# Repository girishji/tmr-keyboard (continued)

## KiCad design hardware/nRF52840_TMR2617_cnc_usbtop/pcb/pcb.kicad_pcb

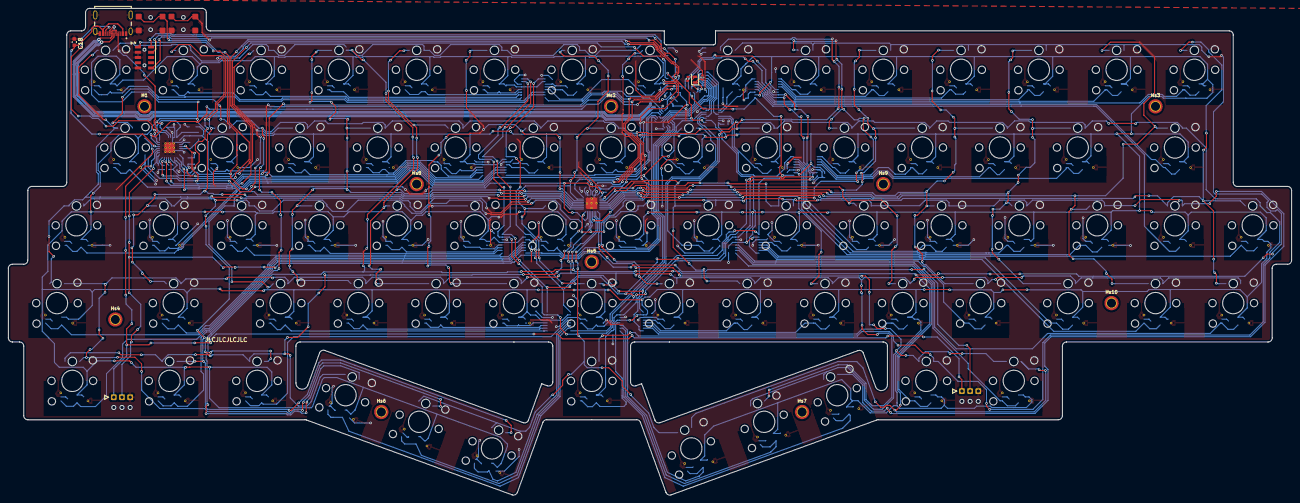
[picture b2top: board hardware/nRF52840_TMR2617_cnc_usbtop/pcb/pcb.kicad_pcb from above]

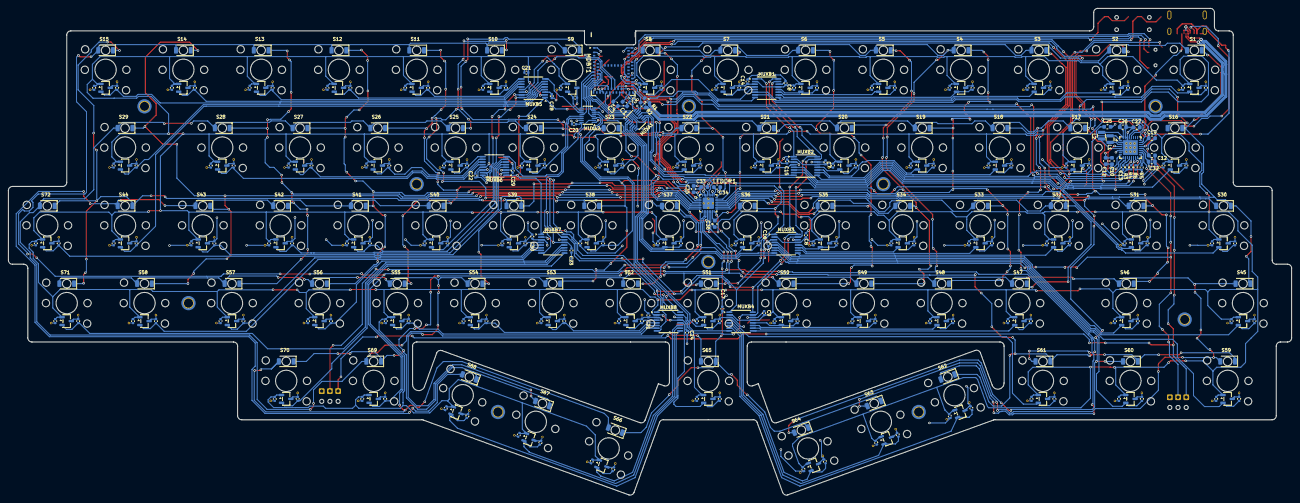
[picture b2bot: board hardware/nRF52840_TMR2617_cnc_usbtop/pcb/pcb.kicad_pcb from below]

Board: 2 copper layers, 313.5 x 118.9 mm, 437 parts (342 on the bottom side), 146 nets.

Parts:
BAT1, BAT2: PCB_Wire_Solder_3p_Connector
C1, C3, C10, C11, C12, C25, C26: 10uF; C_0603_1608Metric
C2, C4: 12pF; C_0402_1005Metric
C5, C6, C7, C8, C9, C14, C15, C16, C17, C20, C21, C22, C23, C24, C28, C29, C30, C31: .1uF; C_0402_1005Metric
C13: 0.1uF; C_0402_1005Metric
C18, C19, C34, C35, C36: 1uF; C_0603_1608Metric
C27, C32: 2.2uF; C_0603_1608Metric
C33: 1nF; C_0603_1608Metric
Cvcc1, Cvcc2, Cvcc3, Cvcc4, Cvcc5, Cvcc6, Cvcc7, Cvcc8, Cvcc9, Cvcc10, Cvcc11, Cvcc12, Cvcc13, Cvcc14, Cvcc15, Cvcc16, Cvcc17, Cvcc18, Cvcc19, Cvcc20, Cvcc21, Cvcc22, Cvcc23, Cvcc24, Cvcc25, Cvcc26, Cvcc27, Cvcc28, Cvcc29, Cvcc30, Cvcc31, Cvcc32, Cvcc33, Cvcc34, Cvcc35, Cvcc36, Cvcc37, Cvcc38, Cvcc39, Cvcc40, Cvcc41, Cvcc42, Cvcc43, Cvcc44, Cvcc45, Cvcc46, Cvcc47, Cvcc48, Cvcc49, Cvcc50, Cvcc51, Cvcc52, Cvcc53, Cvcc54, Cvcc55, Cvcc56, Cvcc57, Cvcc58, Cvcc59, Cvcc60, Cvcc61, Cvcc62, Cvcc63, Cvcc64, Cvcc65, Cvcc66, Cvcc67, Cvcc68, Cvcc69, Cvcc70, Cvcc71, Cvcc72: 0.1uF; C_0402_1005Metric_Cvcc
Cvout1, Cvout2, Cvout3, Cvout4, Cvout5, Cvout6, Cvout7, Cvout8, Cvout9, Cvout10, Cvout11, Cvout12, Cvout13, Cvout14, Cvout15, Cvout16, Cvout17, Cvout18, Cvout19, Cvout20, Cvout21, Cvout22, Cvout23, Cvout24, Cvout25, Cvout26, Cvout27, Cvout28, Cvout29, Cvout30, Cvout31, Cvout32, Cvout33, Cvout34, Cvout35, Cvout36, Cvout37, Cvout38, Cvout39, Cvout40, Cvout41, Cvout42, Cvout43, Cvout44, Cvout45, Cvout46, Cvout47, Cvout48, Cvout49, Cvout50, Cvout51, Cvout52, Cvout53, Cvout54, Cvout55, Cvout56, Cvout57, Cvout58, Cvout59, Cvout60, Cvout61, Cvout62, Cvout63, Cvout64, Cvout65, Cvout66, Cvout67, Cvout68, Cvout69, Cvout70, Cvout71, Cvout72: 0.1nF; C_0402_1005Metric_Cvout
D1, D2, D3, D4, D5, D6, D7, D8, D9, D10, D11, D12, D13, D14, D15, D16, D17, D18, D19, D20, D21, D22, D23, D24, D25, D26, D27, D28, D29, D30, D31, D32, D33, D34, D35, D36, D37, D38, D39, D40, D41, D42, D43, D44, D45, D46, D47, D48, D49, D50, D51, D52, D53, D54, D55, D56, D57, D58, D59, D60, D61, D62, D63, D64, D65, D66, D67, D68, D69, D70, D71, D72: Green LED; LED_1206_3216Metric_ReverseMount_Hole2.1mm
H1: M2_Pad; MountingHole_2.2mm_M2_ISO7380_Pad_TopBottom
Hs2, Hs3, Hs4, Hs5, Hs6, Hs7, Hs8, Hs9, Hs10: M2_Pad; MountingHole_2.2mm_M2_ISO7380_Pad_TopBottom
JLC1: JLC_Order_Num
JTAG1: Conn_ARM_JTAG_SWD_10; SAMTEC-CLP-105-02-X-D-A
Jusb1: USB_TYPE_C_Receptacle_16P; GCT_USB4215-03-A_REVA
L1, L2: 2.2uH; L_Samsung_CIGT201610EH2R2MNE
LEDDR1: LP5864; LP5864-VQFN-32-1EP_4x4mm_P0.4mm_EP2.8x2.8mm_ThermalVias
MDBT1: Raytac_MDBT50Q
MUXA1, MUXA2: TMUX1574DYY; Texas_DYY0016A_TSOT-23-16_2x4.2mm_P0.5mm
MUXB1, MUXB2, MUXB3, MUXB4, MUXB5, MUXB6, MUXB7, MUXB8: TMUX1108PW; TSSOP-16_4.4x5mm_P0.65mm
PMIC1: nPM1300-QEXX; QFN-32-1EP_5x5mm_P0.5mm_EP3.6x3.6mm_ThermalVias
R1, R2: 27R; R_0603_1608Metric
R3, R4: 10k; R_0402_1005Metric
R5, R6: 47k; R_0402_1005Metric
S1, S2, S3, S4, S5, S6, S7, S8, S9, S10, S11, S12, S13, S14, S15, S16, S17, S18, S19, S20, S21, S22, S23, S24, S25, S26, S27, S28, S29, S30, S31, S32, S33, S34, S35, S36, S37, S38, S39, S40, S41, S42, S43, S44, S45, S46, S47, S48, S49, S50, S51, S52, S53, S54, S55, S56, S57, S58, S59, S60, S61, S62, S63, S64, S65, S66, S67, S68, S69, S70, S71, S72: Switch; Gateron_Kailh_Lowpro_Switch
SW1, SW2: SW_DIP_x01; Aliexpress_SW_DIP_TS_1292V_4x6.2x1.8mm
Stb1, Stb2: TMR_switch_stab_2.0u; Stabilizer_Lowpro_2U
TMR1, TMR2, TMR3, TMR4, TMR5, TMR6, TMR7, TMR8, TMR9, TMR10, TMR11, TMR12, TMR13, TMR14, TMR15, TMR16, TMR17, TMR18, TMR19, TMR20, TMR21, TMR22, TMR23, TMR24, TMR25, TMR26, TMR27, TMR28, TMR29, TMR30, TMR31, TMR32, TMR33, TMR34, TMR35, TMR36, TMR37, TMR38, TMR39, TMR40, TMR41, TMR42, TMR43, TMR44, TMR45, TMR46, TMR47, TMR48, TMR49, TMR50, TMR51, TMR52, TMR53, TMR54, TMR55, TMR56, TMR57, TMR58, TMR59, TMR60, TMR61, TMR62, TMR63, TMR64, TMR65, TMR66, TMR67, TMR68, TMR69, TMR70, TMR71, TMR72: TMR2617; SOT-23-3
Y1: 32.768 kHz; Crystal_SMD_2012-2Pin_2.0x1.2mm

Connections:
/AIN0: MDBT1.11 (P0.02/AIN0), MUXA1.4 (D1)
/AIN1: MDBT1.9 (P0.03/AIN1), MUXA1.7 (D2)
/AIN2: MDBT1.20 (P0.04/AIN2), MUXA1.12 (D4)
/AIN3: MDBT1.21 (P0.05/AIN3), MUXA1.9 (D3)
/AIN4: MDBT1.13 (P0.28/AIN4), MUXA2.7 (D2)
/AIN5: MDBT1.10 (P0.29/AIN5), MUXA2.9 (D3)
/AIN6: MDBT1.14 (P0.30/AIN6), MUXA2.4 (D1)
/AIN7: MDBT1.12 (P0.31/AIN7), MUXA2.12 (D4)
/ANA_01: Cvout1.1, MUXB1.7 (S4), TMR1.2 (V_{OUT})
/ANA_02: Cvout2.1, MUXB1.6 (S3), TMR2.2 (V_{OUT})
/ANA_03: Cvout3.1, MUXB1.9 (S8), TMR3.2 (V_{OUT})
/ANA_04: Cvout4.1, MUXB1.10 (S7), TMR4.2 (V_{OUT})
/ANA_05: Cvout5.1, MUXB1.11 (S6), TMR5.2 (V_{OUT})
/ANA_06: Cvout6.1, MUXB1.12 (S5), TMR6.2 (V_{OUT})
/ANA_07: Cvout7.1, MUXB1.4 (S1), TMR7.2 (V_{OUT})
/ANA_08: Cvout8.1, MUXB1.5 (S2), TMR8.2 (V_{OUT})
/ANA_09: Cvout9.1, MUXA2.10 (S3B), TMR9.2 (V_{OUT})
/ANA_10: Cvout10.1, MUXB5.9 (S8), TMR10.2 (V_{OUT})
/ANA_11: Cvout11.1, MUXB5.10 (S7), TMR11.2 (V_{OUT})
/ANA_12: Cvout12.1, MUXB5.11 (S6), TMR12.2 (V_{OUT})
/ANA_13: Cvout13.1, MUXB5.12 (S5), TMR13.2 (V_{OUT})
/ANA_14: Cvout14.1, MUXB5.7 (S4), TMR14.2 (V_{OUT})
/ANA_15: Cvout15.1, MUXB5.6 (S3), TMR15.2 (V_{OUT})
/ANA_16: Cvout16.1, MUXB2.5 (S2), TMR16.2 (V_{OUT})
/ANA_17: Cvout17.1, MUXB2.9 (S8), TMR17.2 (V_{OUT})
/ANA_18: Cvout18.1, MUXB2.10 (S7), TMR18.2 (V_{OUT})
/ANA_19: Cvout19.1, MUXB2.11 (S6), TMR19.2 (V_{OUT})
/ANA_20: Cvout20.1, MUXB2.12 (S5), TMR20.2 (V_{OUT})
/ANA_21: Cvout21.1, MUXB2.4 (S1), TMR21.2 (V_{OUT})
/ANA_22: Cvout22.1, MUXA1.13 (S4B), TMR22.2 (V_{OUT})
/ANA_23: Cvout23.1, MUXA2.6 (S2B), TMR23.2 (V_{OUT})
/ANA_24: Cvout24.1, MUXA2.13 (S4B), TMR24.2 (V_{OUT})
/ANA_25: Cvout25.1, MUXB6.9 (S8), TMR25.2 (V_{OUT})
/ANA_26: Cvout26.1, MUXB6.10 (S7), TMR26.2 (V_{OUT})
/ANA_27: Cvout27.1, MUXB6.11 (S6), TMR27.2 (V_{OUT})
/ANA_28: Cvout28.1, MUXB6.12 (S5), TMR28.2 (V_{OUT})
/ANA_29: Cvout29.1, MUXB5.5 (S2), TMR29.2 (V_{OUT})
/ANA_30: Cvout30.1, MUXB2.7 (S4), TMR30.2 (V_{OUT})
/ANA_31: Cvout31.1, MUXB2.6 (S3), TMR31.2 (V_{OUT})
/ANA_32: Cvout32.1, MUXB3.9 (S8), TMR32.2 (V_{OUT})
/ANA_33: Cvout33.1, MUXB3.10 (S7), TMR33.2 (V_{OUT})
/ANA_34: Cvout34.1, MUXB3.11 (S6), TMR34.2 (V_{OUT})
/ANA_35: Cvout35.1, MUXB3.12 (S5), TMR35.2 (V_{OUT})
/ANA_36: Cvout36.1, MUXA1.6 (S2B), TMR36.2 (V_{OUT})
/ANA_37: Cvout37.1, MUXA1.10 (S3B), TMR37.2 (V_{OUT})
/ANA_38: Cvout38.1, MUXA2.3 (S1B), TMR38.2 (V_{OUT})
/ANA_39: Cvout39.1, MUXB7.4 (S1), TMR39.2 (V_{OUT})
/ANA_40: Cvout40.1, MUXB6.7 (S4), TMR40.2 (V_{OUT})
/ANA_41: Cvout41.1, MUXB6.6 (S3), TMR41.2 (V_{OUT})
/ANA_42: Cvout42.1, MUXB6.5 (S2), TMR42.2 (V_{OUT})
/ANA_43: Cvout43.1, MUXB6.4 (S1), TMR43.2 (V_{OUT})
/ANA_44: Cvout44.1, MUXB5.4 (S1), TMR44.2 (V_{OUT})
/ANA_45: Cvout45.1, MUXB3.5 (S2), TMR45.2 (V_{OUT})
/ANA_46: Cvout46.1, MUXB3.4 (S1), TMR46.2 (V_{OUT})
/ANA_47: Cvout47.1, MUXB4.9 (S8), TMR47.2 (V_{OUT})
/ANA_48: Cvout48.1, MUXB4.10 (S7), TMR48.2 (V_{OUT})
/ANA_49: Cvout49.1, MUXB4.11 (S6), TMR49.2 (V_{OUT})
/ANA_50: Cvout50.1, MUXB4.12 (S5), TMR50.2 (V_{OUT})
/ANA_51: Cvout51.1, MUXA1.3 (S1B), TMR51.2 (V_{OUT})
/ANA_52: Cvout52.1, MUXB8.4 (S1), TMR52.2 (V_{OUT})
/ANA_53: Cvout53.1, MUXB8.5 (S2), TMR53.2 (V_{OUT})
/ANA_54: Cvout54.1, MUXB8.6 (S3), TMR54.2 (V_{OUT})
/ANA_55: Cvout55.1, MUXB8.7 (S4), TMR55.2 (V_{OUT})
/ANA_56: Cvout56.1, MUXB7.12 (S5), TMR56.2 (V_{OUT})
/ANA_57: Cvout57.1, MUXB7.6 (S3), TMR57.2 (V_{OUT})
/ANA_58: Cvout58.1, MUXB7.7 (S4), TMR58.2 (V_{OUT})
/ANA_59: Cvout59.1, MUXB3.6 (S3), TMR59.2 (V_{OUT})
/ANA_60: Cvout60.1, MUXB3.7 (S4), TMR60.2 (V_{OUT})
/ANA_61: Cvout61.1, MUXB4.4 (S1), TMR61.2 (V_{OUT})
/ANA_62: Cvout62.1, MUXB4.7 (S4), TMR62.2 (V_{OUT})
/ANA_63: Cvout63.1, MUXB4.6 (S3), TMR63.2 (V_{OUT})
/ANA_64: Cvout64.1, MUXB4.5 (S2), TMR64.2 (V_{OUT})
/ANA_65: Cvout65.1, MUXB8.12 (S5), TMR65.2 (V_{OUT})
/ANA_66: Cvout66.1, MUXB8.11 (S6), TMR66.2 (V_{OUT})
/ANA_67: Cvout67.1, MUXB8.10 (S7), TMR67.2 (V_{OUT})
/ANA_68: Cvout68.1, MUXB8.9 (S8), TMR68.2 (V_{OUT})
/ANA_69: Cvout69.1, MUXB7.9 (S8), TMR69.2 (V_{OUT})
/ANA_70: Cvout70.1, MUXB7.10 (S7), TMR70.2 (V_{OUT})
/ANA_71: Cvout71.1, MUXB7.11 (S6), TMR71.2 (V_{OUT})
/ANA_72: Cvout72.1, MUXB7.5 (S2), TMR72.2 (V_{OUT})
/CS0: D9.1 (K), D24.1 (K), D38.1 (K), D53.1 (K), LEDDR1.2 (CS0)
/CS1: D10.1 (K), D25.1 (K), D39.1 (K), D54.1 (K), LEDDR1.3 (CS1)
/CS2: D11.1 (K), D26.1 (K), D40.1 (K), D55.1 (K), LEDDR1.4 (CS2)
/CS3: D12.1 (K), D27.1 (K), D41.1 (K), D56.1 (K), LEDDR1.5 (CS3)
/CS4: D13.1 (K), D28.1 (K), D42.1 (K), D57.1 (K), LEDDR1.6 (CS4)
/CS5: D14.1 (K), D29.1 (K), D43.1 (K), D58.1 (K), LEDDR1.7 (CS5)
/CS6: D15.1 (K), D44.1 (K), D71.1 (K), D72.1 (K), LEDDR1.8 (CS6)
/CS7: D67.1 (K), D68.1 (K), D69.1 (K), D70.1 (K), LEDDR1.9 (CS7)
/CS8: D63.1 (K), D64.1 (K), D65.1 (K), D66.1 (K), LEDDR1.10 (CS8)
/CS9: D59.1 (K), D60.1 (K), D61.1 (K), D62.1 (K), LEDDR1.16 (CS9)
/CS10: D1.1 (K), D16.1 (K), D30.1 (K), D45.1 (K), LEDDR1.17 (CS10)
/CS11: D2.1 (K), D17.1 (K), D31.1 (K), D46.1 (K), LEDDR1.18 (CS11)
/CS12: D3.1 (K), D18.1 (K), D32.1 (K), D47.1 (K), LEDDR1.19 (CS12)
/CS13: D4.1 (K), D19.1 (K), D33.1 (K), D48.1 (K), LEDDR1.20 (CS13)
/CS14: D5.1 (K), D20.1 (K), D34.1 (K), D49.1 (K), LEDDR1.21 (CS14)
/CS15: D6.1 (K), D21.1 (K), D35.1 (K), D50.1 (K), LEDDR1.22 (CS15)
/CS16: D7.1 (K), D22.1 (K), D36.1 (K), D51.1 (K), LEDDR1.23 (CS16)
/CS17: D8.1 (K), D23.1 (K), D37.1 (K), D52.1 (K), LEDDR1.24 (CS17)
/GPIO_X: MDBT1.38 (P0.16), PMIC1.10 (GPIO3)
/INT: MDBT1.36 (P0.14), PMIC1.8 (GPIO1)
/LED_DR_EN: C33.1, LEDDR1.32 (VIO_EN), MDBT1.37 (P0.13)
/LOADSW_CTRL: MDBT1.39 (P0.15), PMIC1.9 (GPIO2)
/MUXA_SEL: MDBT1.41 (P0.17), MUXA1.1 (SEL), MUXA2.1 (SEL)
/MUXB_SEL_0: MDBT1.22 (P0.06), MUXB1.1 (A0), MUXB2.1 (A0), MUXB3.1 (A0), MUXB4.1 (A0), MUXB5.1 (A0), MUXB6.1 (A0), MUXB7.1 (A0), MUXB8.1 (A0)
/MUXB_SEL_1: MDBT1.23 (P0.07), MUXB1.16 (A1), MUXB2.16 (A1), MUXB3.16 (A1), MUXB4.16 (A1), MUXB5.16 (A1), MUXB6.16 (A1), MUXB7.16 (A1), MUXB8.16 (A1)
/MUXB_SEL_2: MDBT1.25 (P1.08), MUXB1.15 (A2), MUXB2.15 (A2), MUXB3.15 (A2), MUXB4.15 (A2), MUXB5.15 (A2), MUXB6.15 (A2), MUXB7.15 (A2), MUXB8.15 (A2)
/MUX_B_1: MUXA1.14 (S4A), MUXB1.8 (D)
/MUX_B_2: MUXA1.11 (S3A), MUXB2.8 (D)
/MUX_B_3: MUXA1.5 (S2A), MUXB3.8 (D)
/MUX_B_4: MUXA1.2 (S1A), MUXB4.8 (D)
/MUX_B_5: MUXA2.11 (S3A), MUXB5.8 (D)
/MUX_B_6: MUXA2.14 (S4A), MUXB6.8 (D)
/MUX_B_7: MUXA2.2 (S1A), MUXB7.8 (D)
/MUX_B_8: MUXA2.5 (S2A), MUXB8.8 (D)
/NRESET: JTAG1.10 (~RESET), MDBT1.40 (P0.18/RESET), SW1.2
/SCL: LEDDR1.28 (SCL_SCLK), MDBT1.27 (P0.11), PMIC1.14 (SCL), R3.2
/SDA: LEDDR1.29 (SDA_MOSI), MDBT1.29 (P0.12), PMIC1.13 (SDA), R4.2
/SW0: D1.2 (A), D2.2 (A), D3.2 (A), D4.2 (A), D5.2 (A), D6.2 (A), D7.2 (A), D8.2 (A), D9.2 (A), D10.2 (A), D11.2 (A), D12.2 (A), D13.2 (A), D14.2 (A), D15.2 (A), D62.2 (A), D66.2 (A), D70.2 (A), LEDDR1.11 (SW0)
/SW1: D16.2 (A), D17.2 (A), D18.2 (A), D19.2 (A), D20.2 (A), D21.2 (A), D22.2 (A), D23.2 (A), D24.2 (A), D25.2 (A), D26.2 (A), D27.2 (A), D28.2 (A), D29.2 (A), D61.2 (A), D65.2 (A), D69.2 (A), D72.2 (A), LEDDR1.12 (SW1)
/SW2: D30.2 (A), D31.2 (A), D32.2 (A), D33.2 (A), D34.2 (A), D35.2 (A), D36.2 (A), D37.2 (A), D38.2 (A), D39.2 (A), D40.2 (A), D41.2 (A), D42.2 (A), D43.2 (A), D44.2 (A), D60.2 (A), D64.2 (A), D68.2 (A), LEDDR1.13 (SW2)
/SW3: D45.2 (A), D46.2 (A), D47.2 (A), D48.2 (A), D49.2 (A), D50.2 (A), D51.2 (A), D52.2 (A), D53.2 (A), D54.2 (A), D55.2 (A), D56.2 (A), D57.2 (A), D58.2 (A), D59.2 (A), D63.2 (A), D67.2 (A), D71.2 (A), LEDDR1.14 (SW3)
/SWDCLK: JTAG1.4 (SWCLK/TCK), MDBT1.53 (SWDCLK)
/SWDIO: JTAG1.2 (SWDIO/TMS), MDBT1.51 (SWDIO)
/USB_D+: Jusb1.A6 (D1+), Jusb1.B6 (D2+), R1.2
/USB_D-: Jusb1.A7 (D1-), Jusb1.B7 (D2-), R2.2
/VBAT: BAT1.1 (VBAT), BAT2.1 (VBAT), C32.1, PMIC1.19 (VBAT)
/VBUSOUT: C1.1, C19.1, MDBT1.32 (VBUS), PMIC1.22 (VBUSOUT)
/VDD_nRF: C3.1, C13.2, C25.1, JTAG1.1 (VTref), L1.1, MDBT1.28 (VDD), MDBT1.30 (VDDH), PMIC1.1 (VOUT1), PMIC1.12 (VDDIO), R3.1, R4.1
/VOUT2: C26.1, L2.1, PMIC1.28 (LSIN1/VINLDO1), PMIC1.32 (VOUT2)
/VSYS: C10.1, C11.1, C12.1, C35.1, C36.1, LEDDR1.1 (VCC), LEDDR1.15 (VLED), PMIC1.4 (PVDD), PMIC1.20 (VSYS)
GND: BAT1.3 (GND), BAT2.3 (GND), C1.2, C2.2, C3.2, C4.2, C5.1, C6.1, C7.1, C8.1, C9.1, C10.2, C11.2, C12.2, C13.1, C14.1, C14.2, C15.1, C15.2, C16.1, C16.2, C17.1, C17.2, C18.2, C19.2, C20.1, C21.1, C22.1, C23.1, C24.1, C25.2, C26.2, C27.2, C28.1, C28.2, C29.1, C29.2, C30.1, C30.2, C31.1, C31.2, C32.2, C33.2, C34.1, C35.2, C36.2, Cvcc1.2, Cvcc2.2, Cvcc3.2, Cvcc4.2, Cvcc5.2, Cvcc6.2, Cvcc7.2, Cvcc8.2, Cvcc9.2, Cvcc10.2, Cvcc11.2, Cvcc12.2, Cvcc13.2, Cvcc14.2, Cvcc15.2, Cvcc16.2, Cvcc17.2, Cvcc18.2, Cvcc19.2, Cvcc20.2, Cvcc21.2, Cvcc22.2, Cvcc23.2, Cvcc24.2, Cvcc25.2, Cvcc26.2, Cvcc27.2, Cvcc28.2, Cvcc29.2, Cvcc30.2, Cvcc31.2, Cvcc32.2, Cvcc33.2, Cvcc34.2, Cvcc35.2, Cvcc36.2, Cvcc37.2, Cvcc38.2, Cvcc39.2, Cvcc40.2, Cvcc41.2, Cvcc42.2, Cvcc43.2, Cvcc44.2, Cvcc45.2, Cvcc46.2, Cvcc47.2, Cvcc48.2, Cvcc49.2, Cvcc50.2, Cvcc51.2, Cvcc52.2, Cvcc53.2, Cvcc54.2, Cvcc55.2, Cvcc56.2, Cvcc57.2, Cvcc58.2, Cvcc59.2, Cvcc60.2, Cvcc61.2, Cvcc62.2, Cvcc63.2, Cvcc64.2, Cvcc65.2, Cvcc66.2, Cvcc67.2, Cvcc68.2, Cvcc69.2, Cvcc70.2, Cvcc71.2, Cvcc72.2, Cvout1.2, Cvout2.2, Cvout3.2, Cvout4.2, Cvout5.2, Cvout6.2, Cvout7.2, Cvout8.2, Cvout9.2, Cvout10.2, Cvout11.2, Cvout12.2, Cvout13.2, Cvout14.2, Cvout15.2, Cvout16.2, Cvout17.2, Cvout18.2, Cvout19.2, Cvout20.2, Cvout21.2, Cvout22.2, Cvout23.2, Cvout24.2, Cvout25.2, Cvout26.2, Cvout27.2, Cvout28.2, Cvout29.2, Cvout30.2, Cvout31.2, Cvout32.2, Cvout33.2, Cvout34.2, Cvout35.2, Cvout36.2, Cvout37.2, Cvout38.2, Cvout39.2, Cvout40.2, Cvout41.2, Cvout42.2, Cvout43.2, Cvout44.2, Cvout45.2, Cvout46.2, Cvout47.2, Cvout48.2, Cvout49.2, Cvout50.2, Cvout51.2, Cvout52.2, Cvout53.2, Cvout54.2, Cvout55.2, Cvout56.2, Cvout57.2, Cvout58.2, Cvout59.2, Cvout60.2, Cvout61.2, Cvout62.2, Cvout63.2, Cvout64.2, Cvout65.2, Cvout66.2, Cvout67.2, Cvout68.2, Cvout69.2, Cvout70.2, Cvout71.2, Cvout72.2, JTAG1.3 (GND), JTAG1.5 (GND), JTAG1.9 (GNDDetect), Jusb1.A1 (GND), Jusb1.A12 (GND), Jusb1.B1 (GND), Jusb1.B12 (GND), Jusb1.S1 (SHIELD), LEDDR1.26 (IFS), LEDDR1.27 (VSYNC), LEDDR1.30 (ADDR0_MISO), LEDDR1.31 (ADDR1_SS), LEDDR1.33 (GND), MDBT1.1 (GND@1), MDBT1.2 (GND@2), MDBT1.15 (GND@15), MDBT1.33 (GND@33), MDBT1.55 (GND@55), MUXA1.8 (GND), MUXA1.15 (~EN), MUXA2.8 (GND), MUXA2.15 (~EN), MUXB1.3 (VSS), MUXB1.14 (GND), MUXB2.3 (VSS), MUXB2.14 (GND), MUXB3.3 (VSS), MUXB3.14 (GND), MUXB4.3 (VSS), MUXB4.14 (GND), MUXB5.3 (VSS), MUXB5.14 (GND), MUXB6.3 (VSS), MUXB6.14 (GND), MUXB7.3 (VSS), MUXB7.14 (GND), MUXB8.3 (VSS), MUXB8.14 (GND), PMIC1.2 (PVSS1), PMIC1.6 (PVSS2), PMIC1.30 (LSIN2/VINLDO2), PMIC1.31 (LSOUT2/VOUTLDO2), PMIC1.33 (AVSS), R5.1, R6.1, SW1.1, SW2.1, TMR1.3 (GND), TMR2.3 (GND), TMR3.3 (GND), TMR4.3 (GND), TMR5.3 (GND), TMR6.3 (GND), TMR7.3 (GND), TMR8.3 (GND), TMR9.3 (GND), TMR10.3 (GND), TMR11.3 (GND), TMR12.3 (GND), TMR13.3 (GND), TMR14.3 (GND), TMR15.3 (GND), TMR16.3 (GND), TMR17.3 (GND), TMR18.3 (GND), TMR19.3 (GND), TMR20.3 (GND), TMR21.3 (GND), TMR22.3 (GND), TMR23.3 (GND), TMR24.3 (GND), TMR25.3 (GND), TMR26.3 (GND), TMR27.3 (GND), TMR28.3 (GND), TMR29.3 (GND), TMR30.3 (GND), TMR31.3 (GND), TMR32.3 (GND), TMR33.3 (GND), TMR34.3 (GND), TMR35.3 (GND), TMR36.3 (GND), TMR37.3 (GND), TMR38.3 (GND), TMR39.3 (GND), TMR40.3 (GND), TMR41.3 (GND), TMR42.3 (GND), TMR43.3 (GND), TMR44.3 (GND), TMR45.3 (GND), TMR46.3 (GND), TMR47.3 (GND), TMR48.3 (GND), TMR49.3 (GND), TMR50.3 (GND), TMR51.3 (GND), TMR52.3 (GND), TMR53.3 (GND), TMR54.3 (GND), TMR55.3 (GND), TMR56.3 (GND), TMR57.3 (GND), TMR58.3 (GND), TMR59.3 (GND), TMR60.3 (GND), TMR61.3 (GND), TMR62.3 (GND), TMR63.3 (GND), TMR64.3 (GND), TMR65.3 (GND), TMR66.3 (GND), TMR67.3 (GND), TMR68.3 (GND), TMR69.3 (GND), TMR70.3 (GND), TMR71.3 (GND), TMR72.3 (GND)
unnamed: BAT1.2 (NTC), BAT2.2 (NTC), PMIC1.18 (NTC)
unnamed: Jusb1.A5 (CC1), PMIC1.23 (CC1)
unnamed: Jusb1.B5 (CC2), PMIC1.24 (CC2)
unnamed: C34.2, LEDDR1.25 (VCAP)
unnamed: MDBT1.35 (D+), R1.1
unnamed: MDBT1.34 (D-), R2.1
unnamed: C2.1, MDBT1.17 (P0.00/XL1), Y1.1
unnamed: C4.1, MDBT1.18 (P0.01/XL2), Y1.2
unnamed: PMIC1.15 (SHPHLD), SW2.2
unnamed: L1.2, PMIC1.3 (SW1)
unnamed: L2.2, PMIC1.5 (SW2)
unnamed: C18.1, Jusb1.A4 (VBUS), Jusb1.A9 (VBUS), Jusb1.B4 (VBUS), Jusb1.B9 (VBUS), PMIC1.21 (VBUS)
unnamed: PMIC1.17 (VSET1), R5.2
unnamed: PMIC1.16 (VSET2), R6.2
VCCS: C5.2, C6.2, C7.2, C8.2, C9.2, C20.2, C21.2, C22.2, C23.2, C24.2, C27.1, Cvcc1.1, Cvcc2.1, Cvcc3.1, Cvcc4.1, Cvcc5.1, Cvcc6.1, Cvcc7.1, Cvcc8.1, Cvcc9.1, Cvcc10.1, Cvcc11.1, Cvcc12.1, Cvcc13.1, Cvcc14.1, Cvcc15.1, Cvcc16.1, Cvcc17.1, Cvcc18.1, Cvcc19.1, Cvcc20.1, Cvcc21.1, Cvcc22.1, Cvcc23.1, Cvcc24.1, Cvcc25.1, Cvcc26.1, Cvcc27.1, Cvcc28.1, Cvcc29.1, Cvcc30.1, Cvcc31.1, Cvcc32.1, Cvcc33.1, Cvcc34.1, Cvcc35.1, Cvcc36.1, Cvcc37.1, Cvcc38.1, Cvcc39.1, Cvcc40.1, Cvcc41.1, Cvcc42.1, Cvcc43.1, Cvcc44.1, Cvcc45.1, Cvcc46.1, Cvcc47.1, Cvcc48.1, Cvcc49.1, Cvcc50.1, Cvcc51.1, Cvcc52.1, Cvcc53.1, Cvcc54.1, Cvcc55.1, Cvcc56.1, Cvcc57.1, Cvcc58.1, Cvcc59.1, Cvcc60.1, Cvcc61.1, Cvcc62.1, Cvcc63.1, Cvcc64.1, Cvcc65.1, Cvcc66.1, Cvcc67.1, Cvcc68.1, Cvcc69.1, Cvcc70.1, Cvcc71.1, Cvcc72.1, MUXA1.16 (VDD), MUXA2.16 (VDD), MUXB1.2 (EN), MUXB1.13 (VDD), MUXB2.2 (EN), MUXB2.13 (VDD), MUXB3.2 (EN), MUXB3.13 (VDD), MUXB4.2 (EN), MUXB4.13 (VDD), MUXB5.2 (EN), MUXB5.13 (VDD), MUXB6.2 (EN), MUXB6.13 (VDD), MUXB7.2 (EN), MUXB7.13 (VDD), MUXB8.2 (EN), MUXB8.13 (VDD), PMIC1.29 (LSOUT1/VOUTLDO1), TMR1.1 (V_{CC}), TMR2.1 (V_{CC}), TMR3.1 (V_{CC}), TMR4.1 (V_{CC}), TMR5.1 (V_{CC}), TMR6.1 (V_{CC}), TMR7.1 (V_{CC}), TMR8.1 (V_{CC}), TMR9.1 (V_{CC}), TMR10.1 (V_{CC}), TMR11.1 (V_{CC}), TMR12.1 (V_{CC}), TMR13.1 (V_{CC}), TMR14.1 (V_{CC}), TMR15.1 (V_{CC}), TMR16.1 (V_{CC}), TMR17.1 (V_{CC}), TMR18.1 (V_{CC}), TMR19.1 (V_{CC}), TMR20.1 (V_{CC}), TMR21.1 (V_{CC}), TMR22.1 (V_{CC}), TMR23.1 (V_{CC}), TMR24.1 (V_{CC}), TMR25.1 (V_{CC}), TMR26.1 (V_{CC}), TMR27.1 (V_{CC}), TMR28.1 (V_{CC}), TMR29.1 (V_{CC}), TMR30.1 (V_{CC}), TMR31.1 (V_{CC}), TMR32.1 (V_{CC}), TMR33.1 (V_{CC}), TMR34.1 (V_{CC}), TMR35.1 (V_{CC}), TMR36.1 (V_{CC}), TMR37.1 (V_{CC}), TMR38.1 (V_{CC}), TMR39.1 (V_{CC}), TMR40.1 (V_{CC}), TMR41.1 (V_{CC}), TMR42.1 (V_{CC}), TMR43.1 (V_{CC}), TMR44.1 (V_{CC}), TMR45.1 (V_{CC}), TMR46.1 (V_{CC}), TMR47.1 (V_{CC}), TMR48.1 (V_{CC}), TMR49.1 (V_{CC}), TMR50.1 (V_{CC}), TMR51.1 (V_{CC}), TMR52.1 (V_{CC}), TMR53.1 (V_{CC}), TMR54.1 (V_{CC}), TMR55.1 (V_{CC}), TMR56.1 (V_{CC}), TMR57.1 (V_{CC}), TMR58.1 (V_{CC}), TMR59.1 (V_{CC}), TMR60.1 (V_{CC}), TMR61.1 (V_{CC}), TMR62.1 (V_{CC}), TMR63.1 (V_{CC}), TMR64.1 (V_{CC}), TMR65.1 (V_{CC}), TMR66.1 (V_{CC}), TMR67.1 (V_{CC}), TMR68.1 (V_{CC}), TMR69.1 (V_{CC}), TMR70.1 (V_{CC}), TMR71.1 (V_{CC}), TMR72.1 (V_{CC})

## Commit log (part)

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2025-11-09 A .gitignore A notes/calc.md A notes/components.md A notes/notes.md A sw_prototype/fp-lib-table A sw_prototype/sw_prototype.kicad_pcb A sw_prototype/sw_prototype.kicad_prl A sw_prototype/sw_prototype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
2025-11-16 A border.py M notes/notes.md A pcb/fp-lib-table A pcb/pcb-Edge_Cuts.dxf A pcb/pcb.kicad_pcb A pcb/pcb.kicad_prl A pcb/pcb.kicad_pro A pcb/pcb.kicad_sch A pcb/pcb.step A pcb/sym-lib-table A pickle.py 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
2025-11-16 M .gitignore D pcb/pcb.step
2025-11-21 M border.py M place.py R pcb/~pcb.kicad_pcb.lck -> plate/~plate.kicad_pcb.lck
2025-11-21 M .gitignore D plate/~plate.kicad_pcb.lck
2025-11-21 M border.py M place.py M plate/plate.kicad_pcb M plate/plate.kicad_sch
2025-11-24 A RP2040_Minimal.kicad_sym A RP2040_minimal.pretty/8-USON-Handsolder.kicad_mod A RP2040_minimal.pretty/8-USON.kicad_mod A RP2040_minimal.pretty/C_0402_1005Metric.kicad_mod A RP2040_minimal.pretty/C_0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
2025-11-24 M notes/notes.md
2025-11-30 M border.py M notes/components.md A notes/mcu M pcb/pcb.kicad_pcb M place.py M plate/plate.kicad_pcb M plate/plate.kicad_sch
2025-12-01 M notes/components.md M pcb/pcb.kicad_pcb M pcb/pcb.kicad_sch M place.py D tmr-footprints/sw_lowpro_combo_2u_MDT.kicad_mod D tmr-footprints/sw_lowpro_combo_2u_MDT_L.kicad_mod D tmr-footprints/sw_lowp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
2025-12-02 M border.py A notes/fusion M notes/notes.md
2025-12-03 M border.py A notes/cnc.md M notes/components.md M notes/nRF52840.md M notes/notes.md A notes/parts M pcb/pcb.kicad_pcb M plate/plate.kicad_pcb
2025-12-03 M notes/fusion
2025-12-04 M place.py
2025-12-06 M border.py M notes/notes.md M pcb/pcb.kicad_pcb M pcb/pcb.kicad_prl M pcb/pcb.kicad_pro M pcb/pcb.kicad_sch M pcb/sym-lib-table M place.py M tmr-footprints/C_0603_1608Metric.kicad_mod D tmr-footprin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
2025-12-11 R pickle.py -> dumploc.py M notes/spi M pcb/pcb.kicad_pcb M pcb/pcb.kicad_prl M pcb/pcb.kicad_pro M pcb/pcb.kicad_sch M placefp.py M tmr-footprints/LED-6028.kicad_mod
2025-12-11 M notes/spi M pcb/pcb.kicad_pcb M pcb/pcb.kicad_sch M placefp.py A tracks.py
2025-12-13 M notes/nRF52840.md A notes/soldering M pcb/pcb.kicad_pcb M pcb/pcb.kicad_pro M pcb/pcb.kicad_sch M placefp.py M tmr-footprints/sw_lowpro_gateron_MDT.kicad_mod M tmr-symbols.kicad_sym M tracks.py
2025-12-18 A nordic-lib-kicad-npm.kicad_sym M notes/analog A notes/charging A notes/leds A notes/loadsw R notes/notes.md -> notes/notes A notes/nuts M notes/parts A notes/scan A pcb/LED.kicad_sch M pcb/pcb.kica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
2025-12-21 A notes/bypasscaps A notes/keytravel M notes/leds A notes/muxadc M notes/notes A notes/pulldown M notes/scan A notes/swupdate M pcb/LED.kicad_sch M pcb/pcb.kicad_pcb M pcb/pcb.kicad_prl M pcb/pcb.kic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
2025-12-23 M pcb/pcb.kicad_sch A tmr-footprints/L_Samsung_CIGT201610EH2R2MNE.kicad_mod D tmr-footprints/Murata_DFE201210U.kicad_mod M tmr-symbols.kicad_sym
2025-12-27 M pcb/pcb.kicad_pcb M pcb/pcb.kicad_sch M pcb/switch.kicad_sch M placefp.py A tmr-footprints/Texas_DYY0016A_TSOT-23-16_2x4.2mm_P0.5mm.kicad_mod M tmr-symbols.kicad_sym
2025-12-28 M pcb/pcb.kicad_pcb M pcb/pcb.kicad_prl M pcb/pcb.kicad_pro M pcb/pcb.kicad_sch M pcb/switch.kicad_sch M placefp.py M tracks.py
2025-12-29 M pcb/pcb.kicad_pcb M pcb/pcb.kicad_prl M pcb/pcb.kicad_pro M pcb/pcb.kicad_sch M placefp.py A tmr-footprints/SAMTEC-CLP-105-02-X-D-A-altium.kicad_mod A tmr-footprints/SAMTEC-CLP-105-02-X-D-A.kicad_m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
2025-12-29 M pcb/pcb.kicad_pcb M pcb/pcb.kicad_prl M pcb/pcb.kicad_sch M placefp.py M tmr-footprints/Ezurio_BL54L15_Module.kicad_mod
2026-01-02 M pcb/pcb.kicad_pcb M pcb/pcb.kicad_prl M pcb/pcb.kicad_sch M pcb/switch.kicad_sch M placefp.py A tmr-footprints/Button_Switch_3x4x2.5.kicad_mod A tmr-footprints/Panasonic_EVPAE.kicad_mod
2026-01-02 M pcb/pcb.kicad_pcb M pcb/pcb.kicad_sch A tmr-footprints/MountingHole_2.2mm_M2_ISO7380_Pad_TopBottom.kicad_mod
2026-01-02 M pcb/pcb.kicad_pcb M pcb/pcb.kicad_prl M pcb/pcb.kicad_pro M pcb/pcb.kicad_sch M placefp.py M tmr-footprints/MountingHole_2.2mm_M2_ISO7380_Pad_TopBottom.kicad_mod M tracks.py
2026-01-03 M pcb/pcb.kicad_pcb M pcb/pcb.kicad_prl M pcb/pcb.kicad_pro M placefp.py
2026-01-03 M pcb/pcb.kicad_pcb
2026-01-05 R README.md -> ver1/README.md R RP2040_Minimal.kicad_sym -> ver1/RP2040_Minimal.kicad_sym R RP2040_minimal.pretty/8-USON-Handsolder.kicad_mod -> ver1/RP2040_minimal.pretty/8-USON-Handsolder.kicad_mod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
2026-01-05 M ver2/border.py A ver2/pcb/dxf/pcb-Edge_Cuts.gbr A ver2/pcb/dxf/pcb-job.gbrjob
2026-01-06 M ver2/border.py M ver2/pcb/dxf/pcb-Edge_Cuts.dxf D ver2/pcb/dxf/pcb-Edge_Cuts.gbr D ver2/pcb/dxf/pcb-job.gbrjob M ver2/pcb/pcb.kicad_pcb M ver2/placefp.py A ver2/plate/dxf/plate-Edge_Cuts.dxf M ver2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
2026-01-10 M ver1/border.py M ver1/pcb/pcb.kicad_pcb M ver1/pcb/pcb.kicad_prl M ver1/placefp.py A ver1/plate/plate-Edge_Cuts.dxf M ver1/plate/plate.kicad_pcb M ver1/plate/plate.kicad_prl M ver1/tmr-footprints/D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
2026-01-10 M ver1/pcb/pcb.kicad_pcb M ver1/pcb/pcb.kicad_prl
2026-01-11 M ver1/pcb/pcb-Edge_Cuts.dxf M ver1/pcb/pcb.kicad_pcb M ver1/pcb/pcb.kicad_prl
2026-01-11 M ver1/pcb/pcb-Edge_Cuts.dxf M ver1/pcb/pcb.kicad_pcb M ver1/tmr-footprints/Gateron_Switch_Lowpro.kicad_mod
2026-01-21 A ver3/README.md A ver3/border.py A ver3/dumploc.py A ver3/nordic-lib-kicad-npm.kicad_sym A ver3/pcb/LED.kicad_sch A ver3/pcb/fp-lib-table A ver3/pcb/pcb-eagle-import.kicad_sym A ver3/pcb/pcb.kicad_p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
2026-01-23 M ver3/border.py M ver3/pcb/pcb.kicad_pcb M ver3/pcb/pcb.kicad_sch M ver3/placefp.py M ver3/tmr-footprints/Gateron_Switch_Lowpro.kicad_mod A ver3/tmr-footprints/Gateron_Switch_Lowpro_2.kicad_mod A ve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
2026-01-24 M ver2/border.py M ver2/pcb/pcb.kicad_pcb M ver2/pcb/pcb.kicad_sch M ver2/placefp.py M ver3/border.py
2026-01-26 D bak/border.py D bak/pcb/dxf/pcb-Edge_Cuts.dxf D bak/pcb/pcb.kicad_pcb D bak/pcb/pcb.kicad_prl D bak/pcb/pcb.kicad_pro D bak/pcb/pcb.kicad_sch D bak/placefp.py D bak/plate/dxf/plate-Edge_Cuts.dxf D 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
2026-01-27 M firmware/boards/gp/tmr_kbd_nrf52840/tmr_kbd_nrf52840.dts M firmware/prj.conf M firmware/src/main.c
2026-01-30 M hardware/nRF52840_v1/border.py M hardware/nRF52840_v1/pcb/pcb.kicad_pcb M hardware/nRF52840_v1/pcb/pcb.kicad_prl M hardware/nRF52840_v1/pcb/pcb.kicad_sch M hardware/nRF52840_v1/pcb/switch.kicad_sch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
2026-01-30 D hardware/nRF52840_v1/pcb/usbcover/usbcover.kicad_pcb D hardware/nRF52840_v1/pcb/usbcover/usbcover.kicad_prl D hardware/nRF52840_v1/pcb/usbcover/usbcover.kicad_pro D hardware/nRF52840_v1/pcb/usbcove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
2026-01-31 M hardware/nRF52840_v1/border.py M hardware/nRF52840_v1/pcb/pcb.kicad_pcb M hardware/nRF52840_v1/placefp.py D hardware/nRF52840_v1/plate/plate-Edge_Cuts.dxf M hardware/nRF52840_v1/plate/plate.kicad_p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
2026-02-04 M hardware/nRF52840_v1/placefp.py M hardware/nRF52840_v2/placefp.py M hardware/nRF52840_v2/plate/plate.kicad_pcb M hardware/nRF52840_v2/plate/plate.kicad_prl M hardware/nRF52840_v2/plate/plate.kicad_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
2026-02-05 M hardware/nRF52840_v2/plate/plate.kicad_pcb M hardware/nRF52840_v2/plate/plate.kicad_prl M hardware/nRF52840_v2/plate/plate.kicad_pro A hardware/nRF52840_v2/tmr-footprints/MountingHole_1.8mm_M1.6_No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
2026-02-07 R hardware/nRF52840_v1/README.md -> hardware/nRF52840_aluminum_cnc/README.md R hardware/nRF52840_v2/border.py -> hardware/nRF52840_aluminum_cnc/border.py R hardware/nRF52840_v1/dumploc.py -> hardware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
2026-02-08 M hardware/nRF52840_bakelite_cnc/border.py M hardware/nRF52840_bakelite_cnc/pcb/pcb.kicad_pcb M hardware/nRF52840_bakelite_cnc/pcb/pcb.kicad_prl M hardware/nRF52840_bakelite_cnc/pcb/pcb.kicad_sch A h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
2026-02-08 M hardware/nRF52840_bakelite_cnc/border.py M hardware/nRF52840_bakelite_cnc/pcb/pcb.kicad_pcb M hardware/nRF52840_bakelite_cnc/pcb/pcb.kicad_prl M hardware/nRF52840_bakelite_cnc/pcb/pcb.kicad_pro M h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
2026-02-09 M hardware/nRF52840_bakelite_cnc/border.py A hardware/nRF52840_bakelite_cnc/curves.py M hardware/nRF52840_bakelite_cnc/pcb/pcb.kicad_pcb M hardware/nRF52840_bakelite_cnc/pcb/pcb.kicad_prl
2026-02-10 M hardware/nRF52840_bakelite_cnc/border.py M hardware/nRF52840_bakelite_cnc/pcb/pcb.kicad_pcb M hardware/nRF52840_bakelite_cnc/pcb/pcb.kicad_prl M hardware/nRF52840_bakelite_cnc/pcb/pcb.kicad_pro M h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
2026-02-11 R hardware/nRF52840_bakelite_cnc/README.md -> hardware/nRF52840_plastic_cnc/README.md R hardware/nRF52840_bakelite_cnc/border.py -> hardware/nRF52840_plastic_cnc/border.py R hardware/nRF52840_bakelit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
2026-02-11 M hardware/nRF52840_plastic_cnc/border.py A hardware/nRF52840_plastic_cnc/pcb/pcb-Edge_Cuts.dxf M hardware/nRF52840_plastic_cnc/pcb/pcb.kicad_pcb M hardware/nRF52840_plastic_cnc/pcb/pcb.kicad_prl M h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
2026-02-11 M hardware/nRF52840_plastic_cnc/border.py M hardware/nRF52840_plastic_cnc/pcb/pcb-Edge_Cuts.dxf M hardware/nRF52840_plastic_cnc/pcb/pcb.kicad_pcb M hardware/nRF52840_plastic_cnc/pcb/pcb.kicad_prl M h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
2026-02-13 M hardware/nRF52840_plastic_cnc/border.py M hardware/nRF52840_plastic_cnc/pcb/pcb.kicad_pcb M hardware/nRF52840_plastic_cnc/pcb/pcb.kicad_prl M hardware/nRF52840_plastic_cnc/placefp.py
2026-02-14 A hardware/nRF52840_fr4_cnc/README.md A hardware/nRF52840_fr4_cnc/border.py A hardware/nRF52840_fr4_cnc/curves.py A hardware/nRF52840_fr4_cnc/dumploc.py A hardware/nRF52840_fr4_cnc/nordic-lib-kicad-n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
2026-02-14 M hardware/nRF52840_fr4_cnc/border.py M hardware/nRF52840_fr4_cnc/pcb/pcb.kicad_pcb M hardware/nRF52840_fr4_cnc/pcb/pcb.kicad_prl M hardware/nRF52840_fr4_cnc/placefp.py M hardware/nRF52840_fr4_cnc/tm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
2026-02-14 M hardware/nRF52840_fr4_cnc/plate/plate.kicad_pcb
2026-02-15 R hardware/nRF52840_abs_cnc/README.md -> hardware/nRF52840_cnc_usb_side/README.md R hardware/nRF52840_fr4_cnc/border.py -> hardware/nRF52840_cnc_usb_side/border.py R hardware/nRF52840_abs_cnc/curves.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
2026-02-18 R hardware/nRF52840_cnc_usb_side/README.md -> hardware/nRF52840_cnc_abs/README.md R hardware/nRF52840_cnc_usb_top/border.py -> hardware/nRF52840_cnc_abs/border.py R hardware/nRF52840_cnc_usb_side/cur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
2026-02-23 M hardware/nRF54L15_gateron/pcb/pcb.kicad_prl M hardware/nRF54L15_kailh/border.py M hardware/nRF54L15_kailh/pcb/pcb.kicad_pcb M hardware/nRF54L15_kailh/pcb/pcb.kicad_prl M hardware/nRF54L15_kailh/pcb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
2026-02-25 M hardware/nRF54L15_kailh/border.py A hardware/nRF54L15_kailh/pcb/pcb-F_Fab.dxf M hardware/nRF54L15_kailh/pcb/pcb.kicad_pcb M hardware/nRF54L15_kailh/pcb/pcb.kicad_prl M hardware/nRF54L15_kailh/pcb/p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
2026-02-25 M hardware/nRF54L15_kailh/plate/plate.kicad_pcb
2026-02-26 M .gitignore M hardware/nRF54L15_kailh/border.py M hardware/nRF54L15_kailh/pcb/pcb.kicad_pcb M hardware/nRF54L15_kailh/pcb/pcb.kicad_prl M hardware/nRF54L15_kailh/placefp.py D hardware/nRF54L15_kailh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
2026-02-26 M .gitignore A hardware/resources/MDT-Linear-Sensors-TMR2615x-AAC-Datasheet-EN-V1.3.2.pdf A hardware/resources/MDT-Linear-Sensors-TMR2617S-AAC-Datasheet-EN-V1.1.2.pdf
2026-02-28 M .gitignore M hardware/nRF54L15_kailh/border.py A hardware/nRF54L15_kailh/pat1.kicad_mod A hardware/nRF54L15_kailh/pat1.kicad_sym A hardware/nRF54L15_kailh/pat2.kicad_mod A hardware/nRF54L15_kailh/p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
2026-03-02 M hardware/nRF54L15_kailh/border.py D hardware/nRF54L15_kailh/botcase/botcase-Edge_Cuts.dxf D hardware/nRF54L15_kailh/botcase/botcase-Edge_Cuts.gm1 D hardware/nRF54L15_kailh/botcase/botcase-Edge_Cuts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
2026-03-03 M hardware/nRF54L15_kailh/border.py M hardware/nRF54L15_kailh/botcover/botcover.kicad_pcb M hardware/nRF54L15_kailh/botcover/botcover.kicad_sch M hardware/nRF54L15_kailh/pcb/pcb.kicad_pcb M hardware/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
2026-03-03 M .gitignore A hardware/.gitignore M hardware/nRF54L15_kailh/border.py M hardware/nRF54L15_kailh/botcover/botcover.kicad_pcb M hardware/nRF54L15_kailh/botcover/botcover.kicad_pro
2026-03-03 M hardware/nRF54L15_kailh/botcover/botcover.kicad_pcb
2026-03-06 M .gitignore A hardware/nRF54L15_gateron_kailh_TMR2615/LED.kicad_sch A hardware/nRF54L15_gateron_kailh_TMR2615/fp-lib-table A hardware/nRF54L15_gateron_kailh_TMR2615/nRF54L15_gateron_kailh_TMR2615.ki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
2026-04-06 A hardware/nRF54L15_TMR2615_3dp/border.py A hardware/nRF54L15_TMR2615_3dp/nordic-lib-kicad-npm.kicad_sym R hardware/nRF54L15_gateron_kailh_TMR2615/LED.kicad_sch -> hardware/nRF54L15_TMR2615_3dp/pcb/L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
